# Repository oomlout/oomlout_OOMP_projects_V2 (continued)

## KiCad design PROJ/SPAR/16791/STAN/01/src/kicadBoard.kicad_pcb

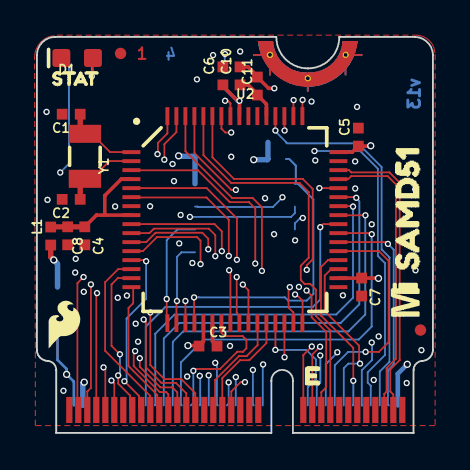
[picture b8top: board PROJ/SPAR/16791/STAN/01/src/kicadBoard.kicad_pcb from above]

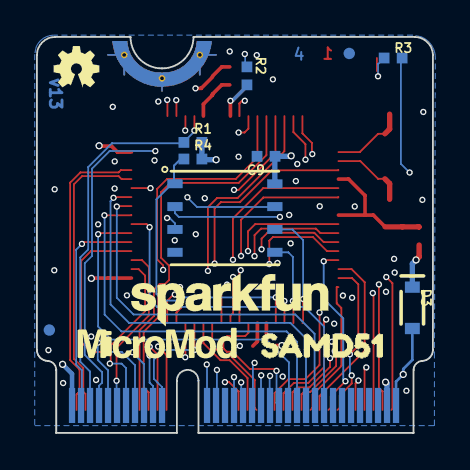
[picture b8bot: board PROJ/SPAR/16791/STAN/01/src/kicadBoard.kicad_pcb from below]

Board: 4 copper layers, 22.0 x 22.0 mm, 36 parts (13 on the bottom side), 57 nets.

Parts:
C1, C2: 15pF; 0402-TIGHT
C3, C5, C6, C7, C9, C10: 0.1uF; 0402-TIGHT
C4, C8: 10uF; 0402-TIGHT
C11: 4.7uF; 0402-TIGHT
D1: BLUE; LED-0603
D3: 1A/23V/620mV; SOD-323
FD5, FD6, FD7, FD8: FIDUCIALUFIDUCIAL; FIDUCIAL-MICRO
FRAME2: FRAME-LEDGER; CREATIVE_COMMONS
J2: MICROMOD-2222; M.2-CARD-E-22
L1: 30Ω; 0402-TIGHT
LOGO2: OSHW-LOGOMINI; OSHW-LOGO-MINI
LOGO5: SPECIAL_INSTRUCTIONS-ORDERING; ORDERING_INSTRUCTIONS
LOGO6: SFE_LOGO_NAME.1_INCH; SFE_LOGO_NAME_.1
R1: 10k; 0402-TIGHT
R2, R3: 1k; 0402-TIGHT
R4: 100k; 0402-TIGHT
U1: W25QXX128MBIT-6X5-NO_CENTER; WSON-8-6X5-NO_CENTERPAD
U2: ATSAMD51J20A-A; TQFP64
U$1: MICROMOD_MI_LOGO_.35
U$4: MICROMOD_LOGO_.35
U$5, U$6: SAMD510
U$7: SFE_LOGO_FLAME_.1
U$8: STAT0
Y1: 32.768kHz; CRYSTAL-SMD-3.2X1.5MM

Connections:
3.3V: C3.1, C5.1, C6.1, C7.1, C9.1, D3.C, J2.72, L1.1, R1.2, R2.2, R4.2, U1.8, U2.21, U2.34, U2.48, U2.56
3.3V_EN: J2.4, U2.38
3.3V_IN: D3.A, J2.2, J2.74
A0/DAC: J2.34, U2.3
A1: J2.38, U2.61
A2/PWM0: J2.32, U2.62
A3/PWM1: J2.47, U2.63
A4: J2.49, U2.64
CIPO: J2.61, U2.15
CIPO1: U1.2, U2.19
COPI: J2.59, U2.13
COPI1: U1.5, U2.18
D0: J2.10, U2.5
D1: J2.18, U2.6
D2/G0: J2.40, U2.9
D3/G1: J2.42, U2.10
D4/G2: J2.44, U2.11
D5/G3: J2.46, U2.12
D6/G4: J2.48, U2.23
D7/G5: J2.73, U2.24
D8/G6: J2.71, U2.25
D9/G7: J2.69, U2.26
D10: J2.67, U2.31
D11: J2.65, U2.32
D13: R3.2, U2.44
D38: J2.43, U2.27
D39: J2.41, U2.28
D+/USBHOST_D+: J2.3, U2.46
D-/USBHOST_D-: J2.5, U2.45
GND: C1.2, C2.2, C3.2, C4.2, C5.2, C6.2, C7.2, C8.2, C9.2, C10.2, C11.2, D1.C, J2.1, J2.7, J2.33, J2.36, J2.39, J2.45, J2.75, J2.GND1, J2.GND2, J2.GND3, U1.4, U2.7, U2.22, U2.33, U2.47, U2.54
HOST_ENABLE: J2.8, U2.51
I2C_~INT: J2.16, U2.37
I2S_CLK: J2.50, U2.39
I2S_FS: J2.52, U2.41
I2S_MCLK: J2.58, U2.40
I2S_SDI: J2.54, U2.43
I2S_SDO: J2.56, U2.42
unnamed: D1.A, R3.1
RXI: J2.19, U2.59
SCK: J2.57, U2.14
SCK1: U1.6, U2.17
SCL: J2.14, U2.35
SCL1/TX2: J2.22, J2.53, U2.29
SDA: J2.12, U2.36
SDA1/RX2: J2.20, J2.51, U2.30
SWDCK: J2.21, R2.1, U2.57
SWDIO: J2.23, U2.58
TXO: J2.17, U2.60
VCC: C10.1, C11.1, U2.53
VDDA: C4.1, C8.1, L1.2, U2.4, U2.8
XIN32: C1.1, U2.1, Y1.P$1
XOUT32: C2.1, U2.2, Y1.P$2
~CS1: R4.1, U1.1, U2.20
~CS: J2.55, U2.16
~HOLD: U1.7, U2.50
~RESET: J2.6, R1.1, U2.52
~WP: U1.3, U2.49

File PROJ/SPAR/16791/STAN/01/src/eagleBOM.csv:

"Part";"Value";"Device";"Package";"Description";"DESIGNER";"PROD_ID";"REV";"VALUE";
"C1";"15pF";"15PF-0402T-50V-5%";"0402-TIGHT";"15pF ceramic capacitors";"";"CAP-13063";"";"15pF";
"C2";"15pF";"15PF-0402T-50V-5%";"0402-TIGHT";"15pF ceramic capacitors";"";"CAP-13063";"";"15pF";
"C3";"0.1uF";"0.1UF-0402T-10V-10%-X7R";"0402-TIGHT";"0.1µF ceramic capacitors";"";"CAP-15083";"";"0.1uF";
"C4";"10uF";"10UF-0402T-6.3V-20%";"0402-TIGHT";"10.0µF ceramic capacitors";"";"CAP-14848";"";"10uF";
"C5";"0.1uF";"0.1UF-0402T-10V-10%-X7R";"0402-TIGHT";"0.1µF ceramic capacitors";"";"CAP-15083";"";"0.1uF";
"C6";"0.1uF";"0.1UF-0402T-10V-10%-X7R";"0402-TIGHT";"0.1µF ceramic capacitors";"";"CAP-15083";"";"0.1uF";
"C7";"0.1uF";"0.1UF-0402T-10V-10%-X7R";"0402-TIGHT";"0.1µF ceramic capacitors";"";"CAP-15083";"";"0.1uF";
"C8";"10uF";"10UF-0402T-6.3V-20%";"0402-TIGHT";"10.0µF ceramic capacitors";"";"CAP-14848";"";"10uF";
"C9";"0.1uF";"0.1UF-0402T-10V-10%-X7R";"0402-TIGHT";"0.1µF ceramic capacitors";"";"CAP-15083";"";"0.1uF";
"C10";"0.1uF";"0.1UF-0402T-10V-10%-X7R";"0402-TIGHT";"0.1µF ceramic capacitors";"";"CAP-15083";"";"0.1uF";
"C11";"4.7uF";"4.7UF-0402_TIGHT-6.3V-20%-X5R";"0402-TIGHT";"4.7µF ceramic capacitors";"";"CAP-14240";"";"4.7uF";
"D1";"BLUE";"LED-BLUE0603";"LED-0603";"Blue SMD LED";"";"DIO-08575";"";"BLUE";
"D3";"1A/23V/620mV";"DIODE-SCHOTTKY-BAT20J";"SOD-323";"Schottky diode";"";"DIO-11623";"";"1A/23V/620mV";
"FD5";"FIDUCIALUFIDUCIAL";"FIDUCIALUFIDUCIAL";"FIDUCIAL-MICRO";"Fiducial Alignment Points";"";"";"";"";
"FD6";"FIDUCIALUFIDUCIAL";"FIDUCIALUFIDUCIAL";"FIDUCIAL-MICRO";"Fiducial Alignment Points";"";"";"";"";
"FD7";"FIDUCIALUFIDUCIAL";"FIDUCIALUFIDUCIAL";"FIDUCIAL-MICRO";"Fiducial Alignment Points";"";"";"";"";
"FD8";"FIDUCIALUFIDUCIAL";"FIDUCIALUFIDUCIAL";"FIDUCIAL-MICRO";"Fiducial Alignment Points";"";"";"";"";
"FRAME2";"FRAME-LEDGER";"FRAME-LEDGER";"CREATIVE_COMMONS";"Schematic Frame - Ledger";"";"";"";"";
"J2";"MICROMOD-2222";"MICROMOD-2222";"M.2-CARD-E-22";"MicroMod Connector";"";"";"";"";
"L1";"30Ω";"FERRITE_BEAD-0402-30Ω-100MHZ";"0402-TIGHT";"Ferrite Bead (blocks, cores, rings, chokes, etc.)";"";"NDUC-15133";"";"30Ω";
"LOGO2";"OSHW-LOGOMINI";"OSHW-LOGOMINI";"OSHW-LOGO-MINI";"Open-Source Hardware (OSHW) Logo";"";"";"";"";
"LOGO5";"SPECIAL_INSTRUCTIONS-ORDERING";"SPECIAL_INSTRUCTIONS-ORDERING";"ORDERING_INSTRUCTIONS";"Special Ordering/Production Instructions Alert";"";"";"";"";
"LOGO6";"SFE_LOGO_NAME.1_INCH";"SFE_LOGO_NAME.1_INCH";"SFE_LOGO_NAME_.1";"SparkFun Font Logo";"";"";"";"";
"R1";"10k";"10KOHM-0402T-1/16W-1%";"0402-TIGHT";"10kΩ resistor";"";"RES-14241";"";"10k";
"R2";"1k";"1KOHM-0402T-1/16W-1%";"0402-TIGHT";"1kΩ resistor";"";"RES-14342";"";"1k";
"R3";"1k";"1KOHM-0402T-1/16W-1%";"0402-TIGHT";"1kΩ resistor";"";"RES-14342";"";"1k";
"R4";"100k";"100KOHM-0402T-1/16W-1%";"0402-TIGHT";"100kΩ resistor";"";"RES-13495";"";"100k";
"U1";"W25QXX128MBIT-6X5-NO_CENTER";"W25QXX128MBIT-6X5-NO_CENTER";"WSON-8-6X5-NO_CENTERPAD";"";"";"IC-15107";"";"";
"U2";"ATSAMD51J20A-A";"ATSAMD51J20A-A";"TQFP64";"";"";"IC-13952";"";"";
"Y1";"32.768kHz";"CRYSTAL-32.768KHZSMD-3.2X1.5";"CRYSTAL-SMD-3.2X1.5MM";"32.768kHz Crystal";"";"XTAL-13062";"";"32.768kHz";
